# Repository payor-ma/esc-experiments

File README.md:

# esc-experiments
A collection of resources for experimenting with the driving of brushless 3 phase motors

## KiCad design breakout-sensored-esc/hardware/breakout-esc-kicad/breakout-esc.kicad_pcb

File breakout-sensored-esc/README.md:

# breakout-sensored-esc

Circuit schematics, sample code and demonstration media for a 3 phase driver bridge with hall effect sensor feedback.  The purpose of this is to breakout the driving hardware of an ESC so that the controller can be replaced with whatever you want, for the sake of developing and testing.  I've used it with an FPGA and an arduino.

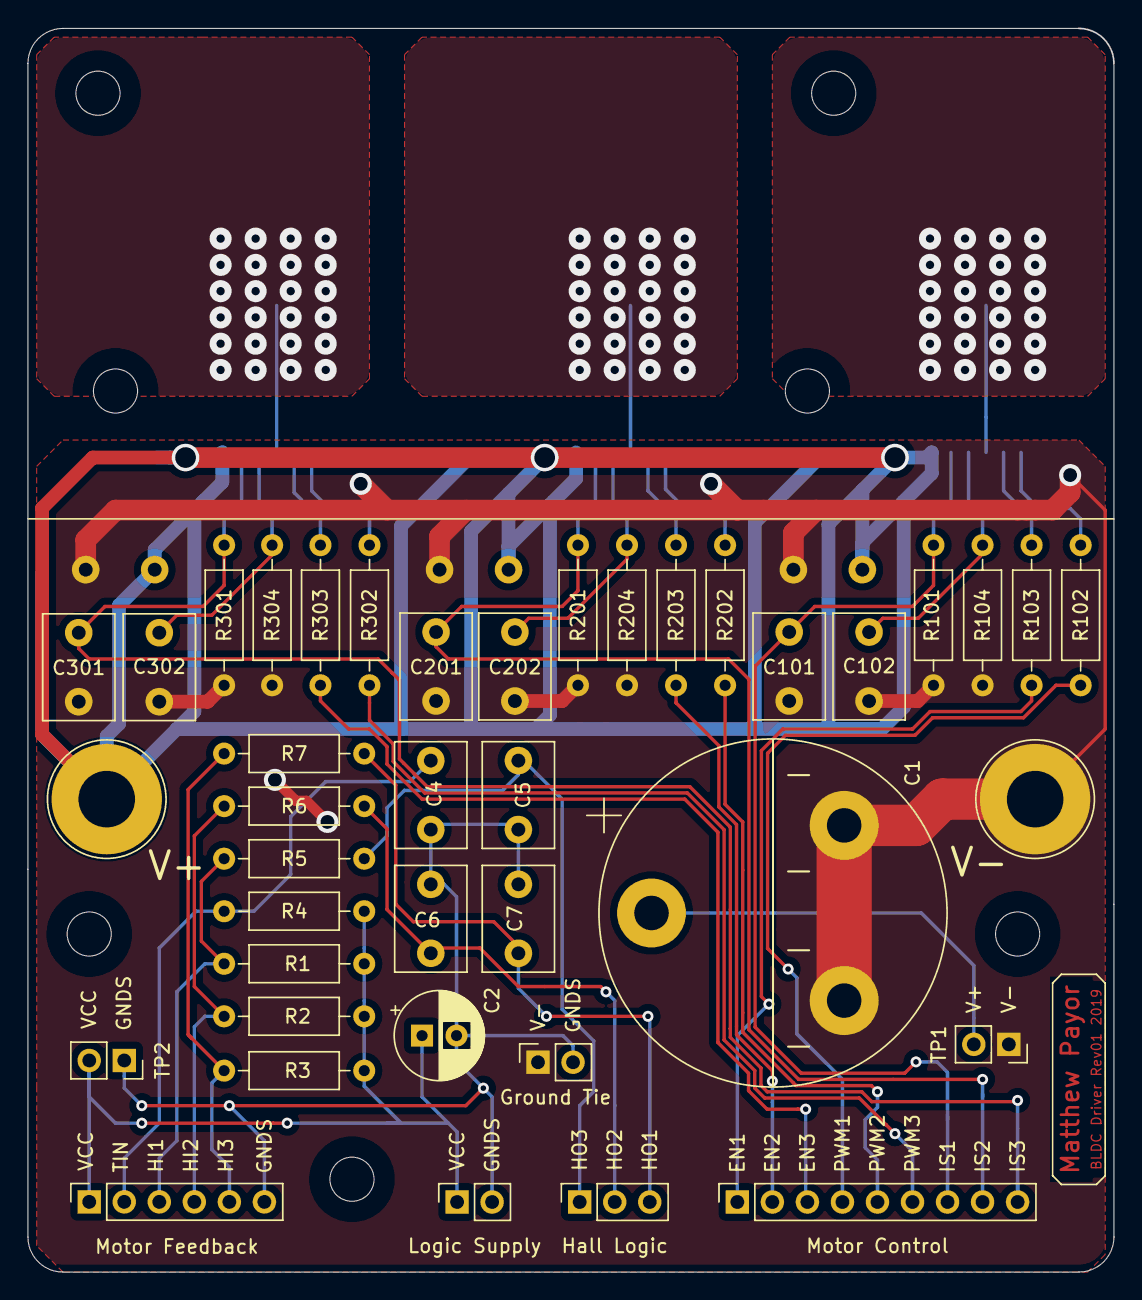
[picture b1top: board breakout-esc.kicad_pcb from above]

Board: 2 copper layers, 78.7 x 90.1 mm, 56 parts (0 on the bottom side), 32 nets.

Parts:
C1: 1000u; CP_Radial_D25.0mm_P10.00mm_3pin_SnapIn
C2: 47u; CP_Radial_D6.3mm_P2.50mm
C4, C5, C6, C7: 4n7; C_Disc_D7.5mm_W5.0mm_P5.00mm
C101, C201, C301: 1n; C_Disc_D7.5mm_W5.0mm_P5.00mm
C102, C202, C302: 47n; C_Disc_D7.5mm_W5.0mm_P5.00mm
C103, C203, C303: 100n; C_Disc_D7.5mm_W5.0mm_P5.00mm
Ground Tie: Ground Tie; PinSocket_1x02_P2.54mm_Vertical
Half Bridge 1, Half Bridge 2, Half Bridge 3: HW-INFINEON_BTN8982; HW-INFINEON_TO263-7-1
Hall Logic: Hall Logic; PinSocket_1x03_P2.54mm_Vertical
Logic Supply: Logic Voltage Input; PinSocket_1x02_P2.54mm_Vertical
Motor Control: Motor Control; PinSocket_1x09_P2.54mm_Vertical
Motor Feedback: Motor Feedback; PinSocket_1x06_P2.54mm_Vertical
PHASE 1, PHASE 2, PHASE 3: Drive; Banana_Jack_1Pin
R1, R2, R3: 2k2; R_Axial_DIN0207_L6.3mm_D2.5mm_P10.16mm_Horizontal
R4: 10k; R_Axial_DIN0207_L6.3mm_D2.5mm_P10.16mm_Horizontal
R5, R6, R7, R101, R102, R103, R104, R201, R202, R203, R204, R301, R302, R303, R304: 1k; R_Axial_DIN0207_L6.3mm_D2.5mm_P10.16mm_Horizontal
TP1: Battery; PinSocket_1x02_P2.54mm_Vertical
TP2: Logic Supply; PinSocket_1x02_P2.54mm_Vertical
V+: Power; Banana_Jack_1Pin
V-: Power; Banana_Jack_1Pin
eee: MountingHole_3.2mm_M3
eee#2, eee#3, eee#4, eee#5, eee#6, eee#7: MountingHole_3.2mm_M3

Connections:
+BATT: C1.1, C103.2, C203.2, C303.2, Half Bridge 1.7, Half Bridge 2.7, Half Bridge 3.7, TP1.2, V+.1
/EN_1: Motor Control.1, R103.1
/EN_2: Motor Control.2, R203.1
/EN_3: Motor Control.3, R303.1
/HIN_1: Motor Feedback.3, R1.1, R5.2
/HIN_2: Motor Feedback.4, R2.1, R6.2
/HIN_3: Motor Feedback.5, R3.1, R7.2
/HOUT_1: C5.1, Hall Logic.1, R5.1
/HOUT_2: C6.1, Hall Logic.2, R6.1
/HOUT_3: C7.1, Hall Logic.3, R7.1
/IS_1: C101.1, Half Bridge 1.6, Motor Control.7, R101.2
/IS_2: C201.1, Half Bridge 2.6, Motor Control.8, R201.2
/IS_3: C301.1, Half Bridge 3.6, Motor Control.9, R301.2
/OUT1: Half Bridge 1.4, Half Bridge 1.TAB, PHASE 1.1
/OUT2: Half Bridge 2.4, Half Bridge 2.TAB, PHASE 2.1
/OUT3: Half Bridge 3.4, Half Bridge 3.TAB, PHASE 3.1
/PWM_1: Motor Control.4, R102.1
/PWM_2: Motor Control.5, R202.1
/PWM_3: Motor Control.6, R302.1
/TIN: C4.1, Motor Feedback.2, R4.1
GND: C1.2, C101.2, C102.1, C103.1, C201.2, C202.1, C203.1, C301.2, C302.1, C303.1, Ground Tie.1, Half Bridge 1.1, Half Bridge 2.1, Half Bridge 3.1, R101.1, R104.1, R201.1, R204.1, R301.1, R304.1, TP1.1, V-.1
GNDS: C2.2, C4.2, C5.2, C6.2, C7.2, Ground Tie.2, Logic Supply.2, Motor Feedback.6, TP2.1
unnamed: C102.2, Half Bridge 1.5, R104.2
unnamed: C202.2, Half Bridge 2.5, R204.2
unnamed: C302.2, Half Bridge 3.5, R304.2
unnamed: Half Bridge 1.2, R102.2
unnamed: Half Bridge 1.3, R103.2
unnamed: Half Bridge 2.2, R202.2
unnamed: Half Bridge 2.3, R203.2
unnamed: Half Bridge 3.2, R302.2
unnamed: Half Bridge 3.3, R303.2
VCC: C2.1, Logic Supply.1, Motor Feedback.1, R1.2, R2.2, R3.2, R4.2, TP2.2

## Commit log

2019-10-24 sorting media
